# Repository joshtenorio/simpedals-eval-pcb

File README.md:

# Sim Racing Pedal Sensor Eval Board
Quick evaluation board I designed to test sensors and write software while I design the mechanical portion for my custom sim racing pedals.

## Features
- DRV5056 - Unipolar hall effect distance sensor
- TMAG6181 - Hall effect angular sensor
- ADS1231 - 24-bit ADC for bridge sensors

## Pictures
TODO

## Manufacturing
BOM coming soon
## License
TODO

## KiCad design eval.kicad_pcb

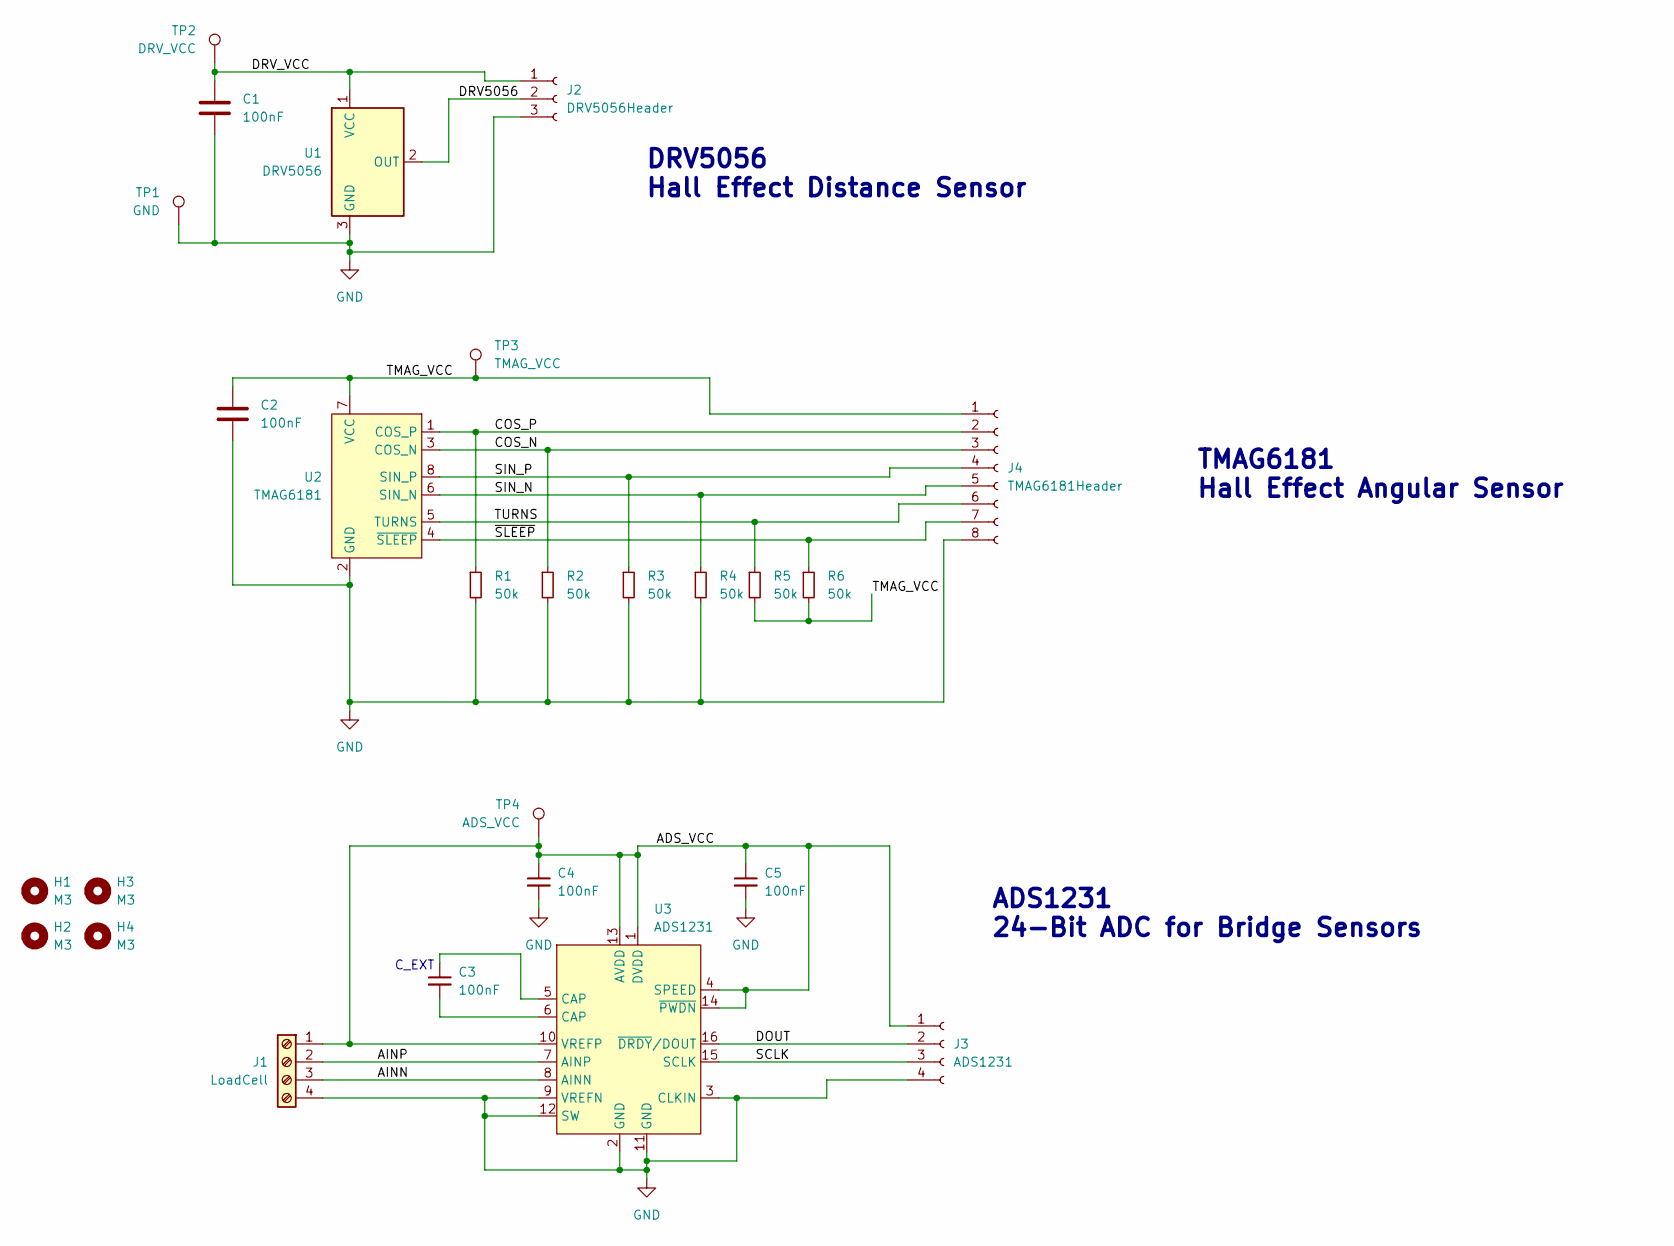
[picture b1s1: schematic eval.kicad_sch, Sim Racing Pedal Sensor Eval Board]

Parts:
C1, C2, C3, C4, C5: 100nF; C_0805_2012Metric
H1, H2, H3, H4: M3; MountingHole_3.2mm_M3
J1: LoadCell; TerminalBlock_TE_282834-4_1x04_P2.54mm_Horizontal
J2: DRV5056Header; PinSocket_1x03_P2.54mm_Vertical
J3: ADS1231; PinSocket_1x04_P2.54mm_Vertical
J4: TMAG6181Header; PinSocket_1x08_P2.54mm_Vertical
R1, R2, R3, R4, R5, R6: 50k; R_0805_2012Metric
TP1: GND; TestPoint_Pad_1.5x1.5mm
TP2: DRV_VCC; TestPoint_Pad_1.5x1.5mm
TP3: TMAG_VCC; TestPoint_Pad_1.5x1.5mm
TP4: ADS_VCC; TestPoint_Pad_1.5x1.5mm
U1: DRV5056; SOT-23
U2: TMAG6181; VSSOP-8_3.0x3.0mm_P0.65mm
U3: ADS1231; SO-16_3.9x9.9mm_P1.27mm

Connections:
/ADS_VCC: C4.1, C5.1, J1.1, J3.1, TP4.1, U3.1 (DVDD), U3.4 (SPEED), U3.10 (VREFP), U3.13 (AVDD), U3.14 (~PWDN)
/AINN: J1.3, U3.8 (AINN)
/AINP: J1.2, U3.7 (AINP)
/COS_N: J4.3, R2.1, U2.3 (COS_N)
/COS_P: J4.2, R1.1, U2.1 (COS_P)
/DOUT: J3.2, U3.16 (~DRDY/DOUT)
/DRV5056: J2.2, U1.2 (OUT)
/DRV_VCC: C1.1, J2.1, TP2.1, U1.1 (VCC)
/SCLK: J3.3, U3.15 (SCLK)
/SIN_N: J4.5, R4.1, U2.6 (SIN_N)
/SIN_P: J4.4, R3.1, U2.8 (SIN_P)
/TMAG_VCC: C2.1, J4.1, R5.2, R6.2, TP3.1, U2.7 (VCC)
/TURNS: J4.6, R5.1, U2.5 (TURNS)
/~SLEEP: J4.7, R6.1, U2.4 (~SLEEP)
GND: C1.2, C2.2, C4.2, C5.2, J1.4, J2.3, J3.4, J4.8, R1.2, R2.2, R3.2, R4.2, TP1.1, U1.3 (GND), U2.2 (GND), U3.2 (GND), U3.3 (CLKIN), U3.9 (VREFN), U3.11 (GND), U3.12 (SW)
unnamed: C3.1, U3.5 (CAP)
unnamed: C3.2, U3.6 (CAP)

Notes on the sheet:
TMAG6181 Hall Effect Angular Sensor
ADS1231 24-Bit ADC for Bridge Sensors
DRV5056 Hall Effect Distance Sensor
C_EXT

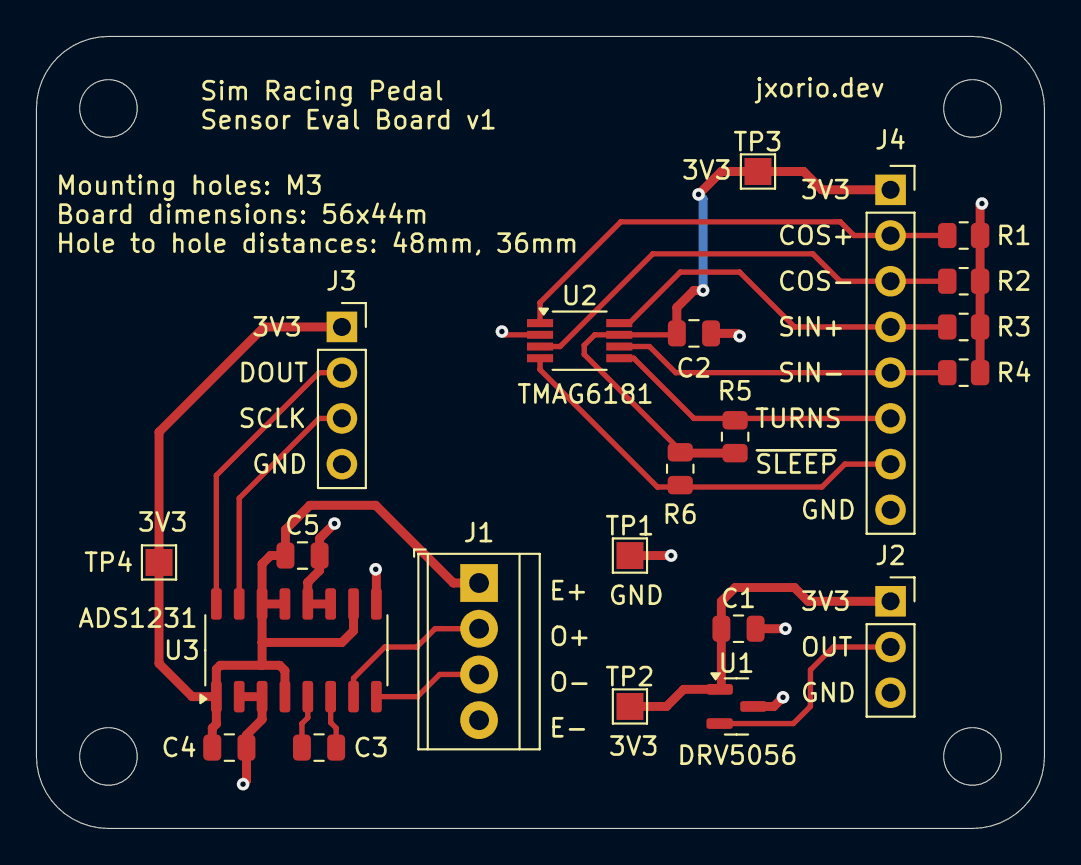
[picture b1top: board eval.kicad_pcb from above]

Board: 2 copper layers, 56.0 x 44.0 mm, 26 parts (0 on the bottom side), 17 nets.
